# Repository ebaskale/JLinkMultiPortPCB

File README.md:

# JLinkMultiPortPCB
JLink Multi Port PCB is home made, DIY project for JLink. It's an adapter for JLink's 20 pins JTAG interface. It can supply 3V3 and 5V power on various debug interfaces such as SWO, ICSP and JTAG. It has power select jumpers for VSupply and also it's can be used disable supply voltage.

## SWO + VSupply
- VTref
- SWCLK
- GND
- SWDIO
- nRESET
- SWO
- VSupply

## ICSP
- NC
- PGC
- PGD
- GND
- VTref
- nRESET

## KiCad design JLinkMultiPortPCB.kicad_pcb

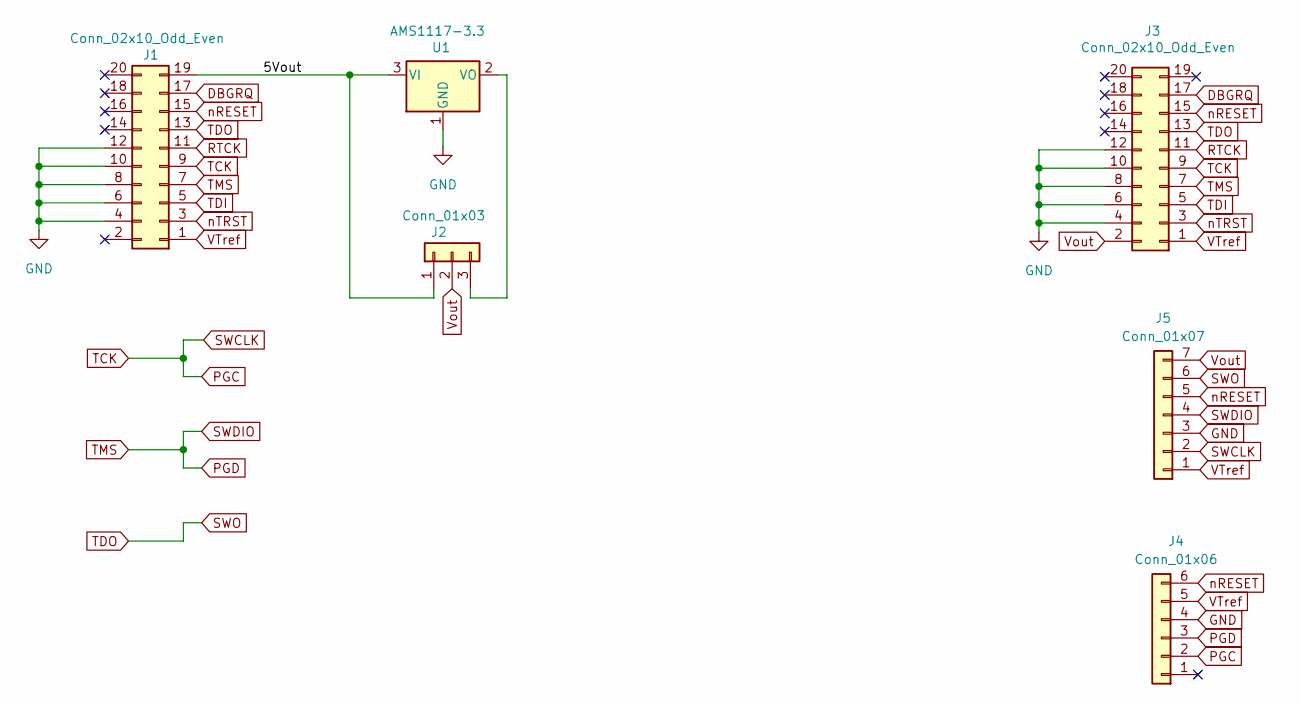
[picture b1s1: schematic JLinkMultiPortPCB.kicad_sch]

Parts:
J1, J3: Conn_02x10_Odd_Even; IDC-Header_2x10_P2.54mm_Horizontal
J2: Conn_01x03; PinHeader_1x03_P2.54mm_Horizontal
J4: Conn_01x06; PinHeader_1x06_P2.54mm_Horizontal
J5: Conn_01x07; PinHeader_1x07_P2.54mm_Horizontal
U1: AMS1117-3.3; SOT-223-3_TabPin2

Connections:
/5Vout: J1.19, J2.1, U1.3 (VI)
DBGRQ: J1.17, J3.17
GND: J1.4, J1.6, J1.8, J1.10, J1.12, J3.4, J3.6, J3.8, J3.10, J3.12, J4.4, J5.3, U1.1 (GND)
unnamed: J2.3, U1.2 (VO)
PGC: J1.9, J3.9, J4.2, J5.2
PGD: J1.7, J3.7, J4.3, J5.4
RTCK: J1.11, J3.11
SWO: J1.13, J3.13, J5.6
TDI: J1.5, J3.5
VTref: J1.1, J3.1, J4.5, J5.1
Vout: J2.2, J3.2, J5.7
nRESET: J1.15, J3.15, J4.6, J5.5
nTRST: J1.3, J3.3

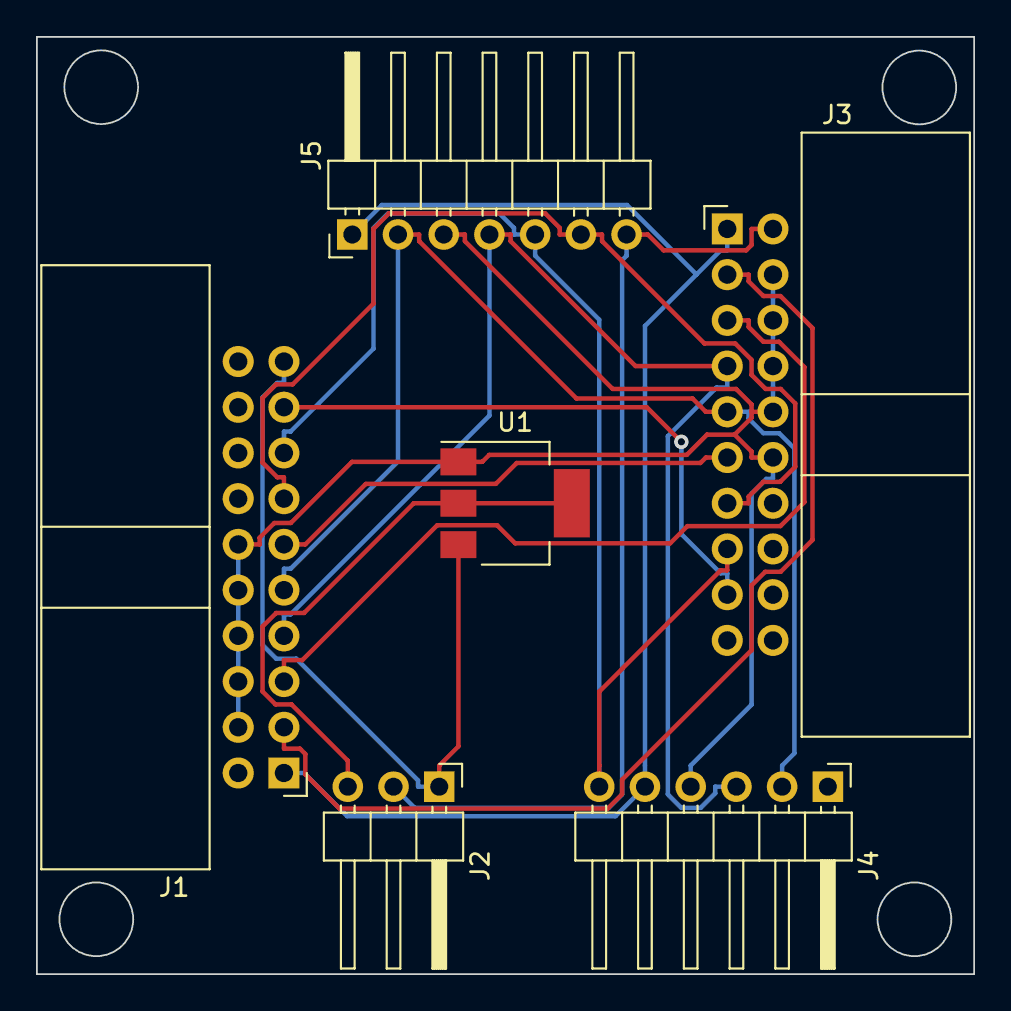
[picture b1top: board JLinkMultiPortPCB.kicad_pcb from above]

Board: 2 copper layers, 52.1 x 52.1 mm, 6 parts (0 on the bottom side), 13 nets.
